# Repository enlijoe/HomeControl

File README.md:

# Description
This is software to manage the electricity usage of a house through monitoring of Tesla Powerwall and local weather.   Inside temperature is adjusted to not use any electricity during peak house.  Will also shed load should a power outage occur and shutdown servers should the Powerwall become low on power during an outage.
This project is growing in scope to be something rather awesome.  If you have knowledge of Java/C/C++/System Verilog/Electrical Engineering/Electronics/Circuit design.  Do you have some of these or all of them or want to learn more about them considering joining this project.
There are many products on the market that can do some of this but there is little to nothing available to allow you to adjust things according to your own needs and most is proprietary and will not work together. Most items are so overpriced that you can build the hardware yourself at a lower cost.  
The Nest Thermostat is a great example of this.  It does not integrate with much if anything at all, it is very expensive and only offers a very small feature set.   Yes many of these items are great for most people but if you want more control then you will love this project
# Current feature set
 - Be able to talk to the Tesla Powerwall REAS API to get usage data
 - Be able to talk to a Weather API to get current and forecasted weather data
 - Be able to talk with custom designed thermostats to monitor and adjust indoor temperature
 - Be able to talk with custom designed power usage monitors to meter power usage at many levels throughout the home
 - Be able to start/stop applications/processes on both windows and Linux systems
 - Be able to start/stop both windows and Linux systems
# Use cases
 - Maximize the power usage during a power outage so that the house is able to withstand an extended grid outage.
 - Monitor home power usage for home business tax reasons.
 - Monitor and adjust power usage for time of use electrical plans where peek and off peek electrical usage differs.
 - Maximize the use of solar power when selling extra power generated is not profitable.
 - Be able to dynamically adjust crypto mining to maximize profits. 

# Java Toolchain
  - Eclipse IDE for Java (2022‑06)
  - Maven
  - Spring Tools 4
  - JDK 17
# ESP32 Tool Chain
 - Eclipse IDE for C/C++ (2022‑06)
 - ESP-IDF Eclipse Plugin see https://github.com/espressif/idf-eclipse-plugin/blob/master/README.md
 - Python 3.7
 - ESP-IDF 4.0
# Hardware Tool Chain
 - KiCad
 
# Dependencies (Other git projects)
Make sure you place all git repos into same base directory as that is an assumption that is made when referencing them
 - KiCadLib (git@github.com:enlijoe/KiCadLib.git)

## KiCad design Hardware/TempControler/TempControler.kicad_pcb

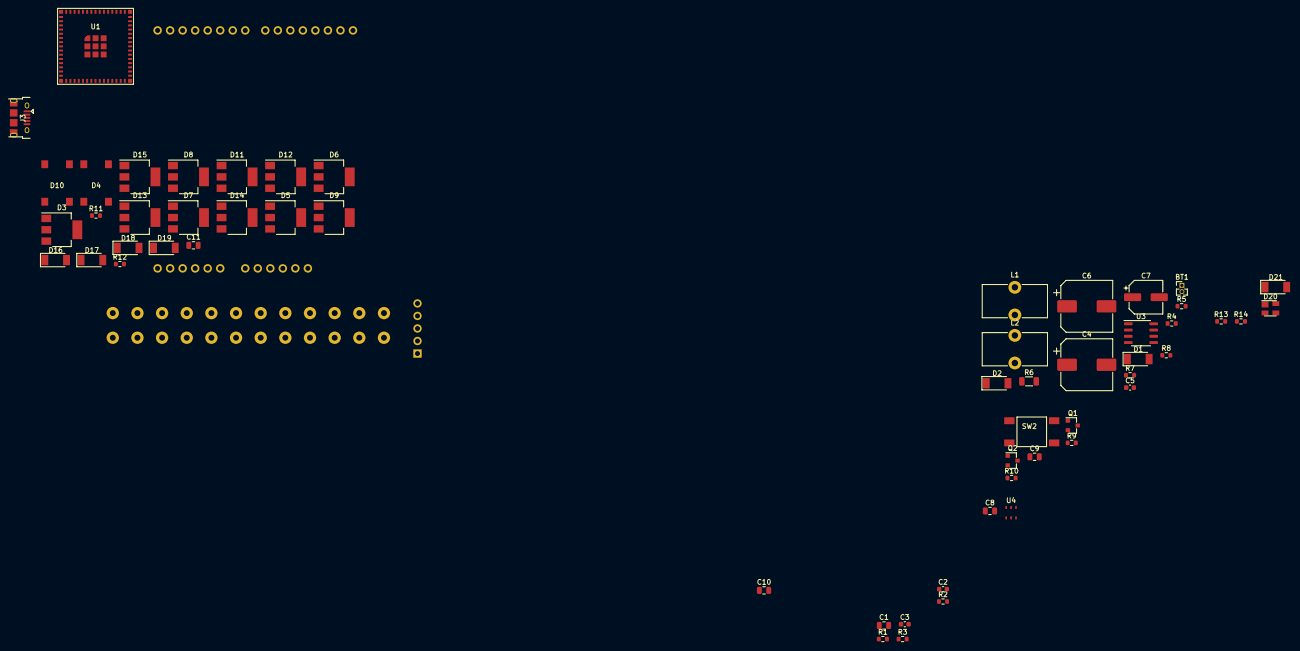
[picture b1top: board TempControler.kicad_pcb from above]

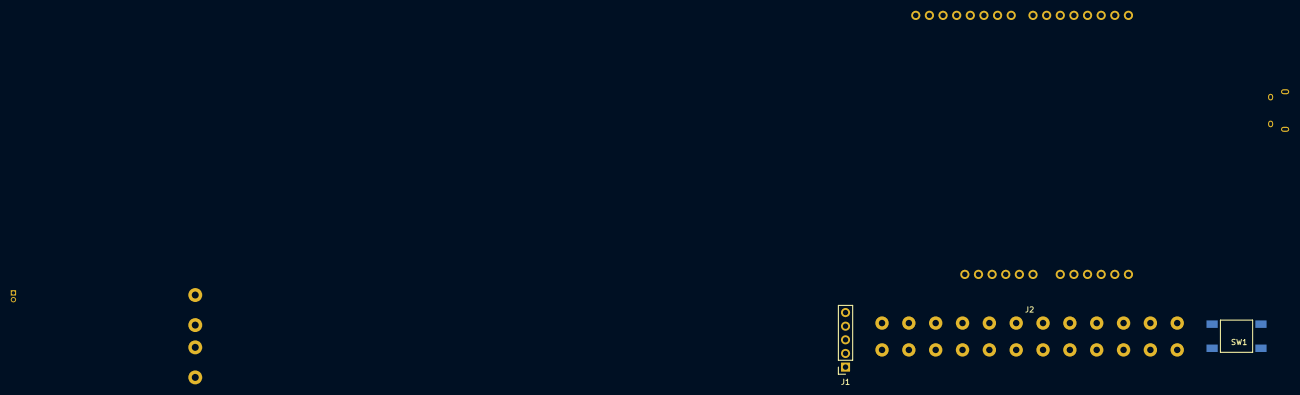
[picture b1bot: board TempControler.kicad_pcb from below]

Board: 2 copper layers, 60 parts (4 on the bottom side), 68 nets, no tracks yet.

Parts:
BT1: Battery; PinHeader_1x02_P1.27mm_Vertical
C1, C8, C9, C10, C11: .1uF; C_0805_2012Metric
C2, C3: 22uF; C_0603_1608Metric
C4, C6: 470uF; CP_Elec_10x10
C5: 470pF; C_0603_1608Metric
C7: 100uF; CP_Elec_6.3x5.8
D1, D2, D16, D18, D21: RB080LAM-30TR; D_SOD-128
D3, D5, D6, D7, D8, D9, D11, D12, D13, D14, D15: Z0109NN6AA4; SOT-223-3_TabPin2
D4, D10: D_Bridge_+-AA; DBF-4
D17, D19: 3V; D_SOD-128
D20: SP0503BAHT; SOT-143
J1: Conn_01x05_Male; PinSocket_1x05_P2.54mm_Vertical
J2: Conn_01x12_Male; TerminalBlock_CUI-12_P5mm
J3: USB_B_Micro; USB_Micro-B_Amphenol_10118194-0011LF_Horizontal
L1: 100uH; L_Toroid_Vertical_L13.0mm_W6.5mm_P5.60mm
L2: 1uH; L_Toroid_Vertical_L13.0mm_W6.5mm_P5.60mm
Q1, Q2: Q_NPN_BEC; SOT-23
R1, R2, R3, R4, R5, R9, R10, R14: 10k; R_0603_1608Metric
R6: .1; R_1206_3216Metric
R7: 22.1k; R_0603_1608Metric
R8: 36k; R_0603_1608Metric
R11, R12: 56k; R_0603_1608Metric
R13: 5.6k; R_0603_1608Metric
SW1, SW2: SW_Push; button SMD
U1: ESP32­S3­MINI; ESP32-S3-MINI-1
U2: MAR3501; Shield_MEGA-LCD
U3: AP34063S8L-13; SO-8_3.9x4.9mm_P1.27mm
U4: HS300x; LGA-6_2.4x3mm_P1mm

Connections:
+3V3: C2.1, C3.1, C7.1, L2.2, R1.2, R2.1, U1.3, U2.3V3, U4.4
+24V: C4.1, D1.1, D4.1, D10.1, D21.1, R6.2, U3.6
/Display/CS: U1.44, U2.A3
/Display/D0: U1.32, U2.D8
/Display/D1: U1.31, U2.D9
/Display/D2: U1.30, U2.D2
/Display/D3: U1.29, U2.D3
/Display/D4: U1.28, U2.D4
/Display/D5: U1.27, U2.D5
/Display/D6: U1.26, U2.D6
/Display/D7: U1.25, U2.D7
/Display/RD: U1.41, U2.A0
/Display/RS: U1.12, U2.A2
/Display/WR: U1.5, U2.A1
/Display/~Reset: U1.6, U2.A4
/ESP32/Attach: R13.1, R14.1, U1.16
/ESP32/B_Sel: D13.3, U1.15
/ESP32/D+: D20.3, J3.3, U1.24
/ESP32/D-: D20.2, J3.2, U1.23
/ESP32/E_Ctl: D5.3, U1.37
/ESP32/Enable: C9.1, Q1.3, R2.2, SW2.2, U1.45
/ESP32/G_Ctl: D8.3, U1.10
/ESP32/OB_Ctl: D9.3, U1.11
/ESP32/O_Sel: D11.3, U1.14
/ESP32/PGM: Q2.2, U1.4
/ESP32/RX: J1.4, U1.40
/ESP32/Rc_Sence: C10.1, D17.1, R11.1, U1.19
/ESP32/SCL: U1.22, U4.1
/ESP32/SDA: U1.21, U4.2
/ESP32/S_Ctl: D15.3, U1.13
/ESP32/TX: J1.5, U1.39
/ESP32/W1_Ctl: D14.3, U1.33
/ESP32/W2_Ctl: D12.3, U1.34
/ESP32/WiFiSetup: C1.1, R1.1, SW1.2, U1.9
/ESP32/X_Ctl: D3.3, U1.38
/ESP32/Y1_Ctl: D7.3, U1.35
/ESP32/Y2_Ctl: D6.3, U1.36
/ESP32/bSence: R4.2, R5.1, U1.17
/Serial Programmer/DTR: J1.3, Q2.3, R9.1
/Serial Programmer/RTS: J1.2, Q1.2, R10.1
/Thermostat/C: D4.3, D10.3, J2.1
/Thermostat/E: D6.1, J2.10
/Thermostat/G: D9.1, J2.7
/Thermostat/OB: D12.1, J2.6
/Thermostat/Rc: D3.2, D7.2, D8.2, D10.4, D11.2, D18.2, J2.3
/Thermostat/Rc_Sence: C11.1, D19.1, R12.1, U1.18
/Thermostat/Rh: D4.4, D5.2, D6.2, D9.2, D13.1, D14.2, D15.2, D16.2, J2.2
/Thermostat/S1S2: D3.1, J2.12
/Thermostat/W1: D15.1, J2.4
/Thermostat/W2: D14.1, J2.5
/Thermostat/X: D5.1, J2.11
/Thermostat/Y1: D8.1, J2.8
/Thermostat/Y2: D7.1, J2.9
/USB/VBus: D20.4, D21.2, J3.1, R13.2
GND: BT1.2, C1.2, C2.2, C3.2, C4.2, C5.2, C6.2, C7.2, C8.2, C9.2, C10.2, C11.2, D2.2, D4.2, D10.2, D17.2, D19.2, D20.1, J1.1, J3.5, J3.6, R3.2, R5.2, R7.2, R14.2, SW1.1, SW2.1, U1.1, U1.2, U1.42, U1.43, U1.46, U1.47, U1.48, U1.49, U1.50, U1.51, U1.52, U1.53, U1.54, U1.55, U1.56, U1.57, U1.58, U1.59, U1.60, U1.61, U1.62, U1.63, U1.64, U1.65, U3.4, U4.6
unnamed: BT1.1, D1.2, R4.1
unnamed: C5.1, U3.3
unnamed: C6.1, L1.2, L2.1, R8.1
unnamed: C8.1, U4.3
unnamed: D2.1, L1.1, U3.2
unnamed: D11.1, D12.2, D13.2
unnamed: D16.1, R11.2
unnamed: D18.1, R12.2
unnamed: Q1.1, R9.2
unnamed: Q2.1, R10.2
unnamed: R3.1, U1.7
unnamed: R6.1, U3.1, U3.7, U3.8
unnamed: R7.1, R8.2, U3.5

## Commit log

2022-07-16 Initial Project Setup
2022-07-16 Updates to add more info
2022-07-16 Created Hardware Project
2022-07-16 Initial Project Creation
2022-07-16 Missed file in Project Creation.
2022-07-16 Built project for first time
2022-07-17 initial controller and jpa setup
2022-07-17 Added Eclipse IDE Versions
2022-07-17 Changed port number on web server
2022-07-17 Updated to include KiCad dependency on KiCadLib
2022-07-18 Working on design
2022-07-24 Basic Entity Creation
    Added Entity folder with meters and systemStatus entities.
2022-07-24 Private Fields for Entities
    Added Private Fields to each of the entites.
    Unsure about the meters fields.
2022-07-24 Updated properties
2022-07-24 Completed entites
    Finished up the fields in the entites.
    Added Getters and Setters, and the Constructors
2022-07-24 removed super() from Parameterized Constructor
2022-07-24 Reformatted Entites
    Removed redundant comments and using Long Object instead of long primitive type.
    Discard the usages of _, and using camel case instead.
2022-07-24 DAOs Creation
    Added DAOs for each entities. Also updated some naming schemes of the entities.
2022-07-24 Schematic Complete
    DRC - Done
    Schematic - Done
    Values - Done
    Part Selection - In Progress
    Footprint assignment- In Progress
2022-07-24 Delete Foo.java
    Junk should not have been added
2022-07-24 Delete TestEntity.java
    Trash File
2022-07-24 Delete NewONe.java
    Trash Cleanup
2022-07-24 Ops checked in bad code
2022-07-24 Delete SiteDao.java
    Ops not real code cleanup
2022-07-24 More bad commit
2022-07-30 All Part Numbers Selected
    Next step select all footprints
2022-07-31 Footprints selected
    On to board design
2022-08-11 Update README.md
    Added more info and corrected spelling errors
2022-08-18 Create Worker.java
    Create the basic worker thread class. It will be the class that calls the services.
